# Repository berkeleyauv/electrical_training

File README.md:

# Underwater Robotics @ Berkeley | Electrical Training

Hello there! Welcome to UR@B electrical team! UR@B Electrical training will introduce you to basic circuit concepts, and firmware. Additionally, the HOPE Decal content created by IEEE @ Berkeley will introduce you to printed circuit board CAD tools. 

> "*Note: Feel free too ask/wait for a electrical team member to help you when working on this training to prevent frustration.*"

> "*Note: If you already feel comfortable with all the concepts below, feel free to skip this whole training all together and work on the project*"

### Prerequisites:
- None

At the end of the training, you will know: 

1. Basic Circuit (Electronic) Concepts
2. Basic Printed Circuit Board Design (PCB) CAD Tools 

### High Level View:

In the electrical team, you will be creating the electronics and the associated software to make it work. 

<br>

> "*Note: For each part, click on the dropdown to show the content.*"

# Prelab: Electronics (Hardware) - Part 1

You will learn about the concept of ground, voltage, current and various machine tools used in electrical engineering. 

<details>
<summary>Electronics Dropdown</summary>

## Current
Current is the rate at which electrons (particles) flow. Remember that particles are physical in nature. 

## Voltage 
Particles will stay still unless there is enough pressure to get them moving. Voltage is the difference in electric potential energy between two points. 
It is the **"Push"** that gives pressure to push electrons (particles) through a circuit. 

## Reference Voltage (Ground) 

Reference voltage commonly referred to as **ground** is a value that can be used with respect to everything else. 
One example is that "Earth ground" can be used as the reference voltage but most times the reference voltage is relative to the application. 

</br>

**"Common" ground** is the reference voltage that is shared across
the whole application. 

> **V_GND = 0 V**

Most times, zero volts are used as the reference voltage to make calculations easier.  

Note that the reference voltage may not necessarily be 0 volts, It can be any value as long as the circuit designer is consistent. 

## Resistance
Resistance is the opposition to the flow of current. Everything has resistance including wires itself. 

## Ohm Law

Image Credits: Build-electronics-circuit / Oyvind Nydal Dahl

</br>

Bringing it all together with Ohm's Law.  

> Voltage = Current * Resistance
 
> Current = Voltage / Resistance

> Resistance = Voltage / Current 

## Hardware Equipment
> Note: Please ask if you are interested in getting hands on experience with these machines.

### Power Supply Unit
Power supply unit provide a voltage source. 

### Multimeter
Measures Voltage, Current, and Resistance.

### Oscilloscope
Mainly used for tracking "signals". Signals are just voltage values. Oscilloscope is a multimeter but is able to provide a graph of the signal over time. 

</details>

> Checkpoint: No Checkpoint for Part 1

# Datasheet - Part 2 
When you are making anything, you are often not creating everything from scratch. You will need to use technical manuals, reference sheets, datasheets to know various features of "devices" that you plan on using in a design.

For example, consider a LED. 

There is a voltage value that the LED must be used to get the LED to turn on. This voltage value is called the "forward voltage". 
Consider: https://learn.adafruit.com/all-about-leds/the-led-datasheet
If you look at the datasheet, you will find that the "forward voltage" is 1.85V. That means the voltage difference across the LED should be that voltage value.

Note: Classes, Search engines, and books are your best friend in figuring out what various attributes you need to know when designing. 

Naturally, you are effectively required to search for information on your own because no one knows the exact information that is required.

Additionally, to make the LED work, you need to add a resistor. The point of the resistor is to limit the current. `R = 150Ohm - 300 Ohm` will work. The resistance depends on how intense the LED you want and minimum LED values.

# PCB ECAD Tools - KICAD - Part 3

Instead of using prototyping boards like stripboards and breadboards, you will now create a "PCB" which makes your electronics much more versatile. Instead of wires failing off, the wires can't fall off printed circuit boards. Like how 3D Printing design uses CAD tools like Solidworks, electrical engineers use electronic computer aided design (ECAD) like KiCad. 

<details>
<summary>PCB ECAD Tools Dropdown</summary>

To get used to the KiCad ECAD software, please follow the HOPE course. 
#### Hands on PCB Engineering (HOPE) | IEEE @ Berkeley
IEEE @ Berkeley has created an awesome decal (course) on printed circuit board design. All content and credit goes to HOPE staff!

See HOPE Decal- https://ieee.berkeley.edu/hope/
If the link does not work, please search for: IEEE Berkeley HOPE Decal
<br>

<h1>Disclaimer: We use "Altium Designer" </h1>
<b>But doing the training in KiCad is much easier. Altium is just another
ECAD tool but it isn't that intuitive to use. </b>

</br>

**For underwater robotics, Please do the following content and associated labs:**
1. Install Kicad
2. Light Sensor Schematic
3. Light Sensor Components
4. Light Sensor Layout
5. USB Charger Components (Optional)
6. USB Charger Schematic (Optional)
7. USB Charger Layout (Optional)

</details>

> Checkpoint: The DRC for both schematic/layout should show no errors. DRC - Design Rule Checker.

# Design
We did not at all cover the "Design" aspect of electrical engineering, searching for answers through your coursework, using search engines, and asking questions are the best way to learn "Design". 

Here are some keywords that outlines the steps to make a design work:
1. Planning
2. Tapeout
3. Bringup
4. Implementation

# Notes
The training and project is not meant to be comprehensive. Hopefully the training and project is good enough as a launchpad for you to further investigate engineering.

# Other:

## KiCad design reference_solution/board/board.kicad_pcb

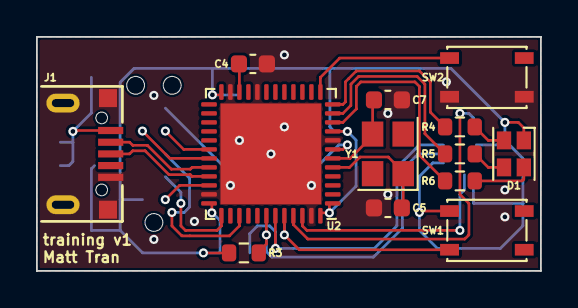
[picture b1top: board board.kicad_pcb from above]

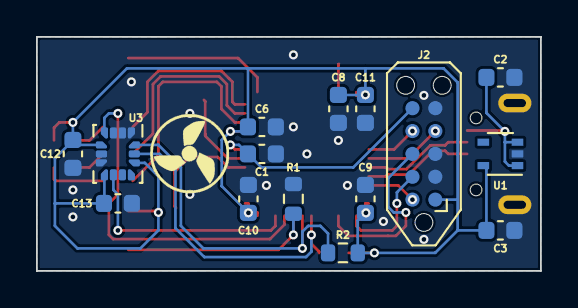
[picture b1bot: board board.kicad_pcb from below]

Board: 2 copper layers, 28.0 x 13.0 mm, 29 parts (16 on the bottom side), 26 nets.

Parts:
C1, C6, C8, C9, C10, C12, C13: 100n; C_0603_1608Metric
C2, C3: 1u; C_0603_1608Metric
C4, C11: 4.7u; C_0603_1608Metric
C5, C7: 20p; C_0603_1608Metric
D1: LED_ARGB; LED_Cree-PLCC4_2x2mm_CW
H1: logo; auv_logo
J1: USB_B_Micro; USB_Micro-B_U254-05
J2: SWD/UART; Tag-Connect_TC2050-IDC-NL_2x05_P1.27mm_Vertical
R1, R2, R3: 10k; R_0603_1608Metric
R4, R5, R6: 150; R_0603_1608Metric
SW1: BOOT0; SW_SPST_PTS810
SW2: USR; SW_SPST_PTS810
U1: MIC5365-3.3YC5; SOT-353_SC-70-5
U2: STM32F401CEUx; QFN-48-1EP_7x7mm_P0.5mm_EP5.6x5.6mm
U3: LSM6DSM; LGA-14_3x2.5mm_P0.5mm_LayoutBorder3x4y
Y1: 8MHz; Crystal_SMD_3225-4Pin_3.2x2.5mm

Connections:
+3V3: C3.1, C6.2, C8.1, C9.1, C10.1, C11.1, C12.1, C13.1, D1.1 (A), J2.1, R2.2, R3.2, SW1.2 (B), U1.5 (VOUT), U2.1 (VBAT), U2.9 (VREF+), U2.24 (VDD), U2.36 (VDD), U2.48 (VDD), U3.5 (VDDIO), U3.8 (VDD), U3.12 (CS)
+5V: C2.2, J1.1 (VBUS), U1.1 (VIN), U1.3 (EN)
/BOOT0: R1.1, SW1.1 (A), U2.44 (BOOT0)
/D+: J1.3 (D+), U2.33 (PA12)
/D-: J1.2 (D-), U2.32 (PA11)
/INT1: U2.45 (PB8), U3.4 (INT1)
/INT2: U2.46 (PB9), U3.9 (INT2)
/LED_B: R4.1, U2.12 (PA2)
/LED_G: R5.1, U2.11 (PA1)
/LED_R: R6.1, U2.10 (PA0)
/NRST: C1.1, J2.6, U2.7 (NRST)
/RX: J2.4, U2.31 (PA10)
/SCL: R3.1, U2.42 (PB6), U3.13 (SCL)
/SDA: R2.1, U2.43 (PB7), U3.14 (SDA)
/SWCLK: J2.9, U2.37 (PA14)
/SWDIO: J2.10, U2.34 (PA13)
/SWO: J2.8, U2.39 (PB3)
/TX: J2.7, U2.30 (PA9)
/USR_BUT: SW2.2 (B), U2.13 (PA3)
GND: C1.2, C2.1, C3.2, C4.1, C5.1, C6.1, C7.2, C8.2, C9.2, C10.2, C11.2, C12.2, C13.2, J1.5 (GND), J1.6 (Shield), J2.2, J2.3, J2.5, R1.2, SW2.1 (A), U1.2 (GND), U2.8 (VSSA), U2.20 (PB2), U2.23 (VSS), U2.35 (VSS), U2.47 (VSS), U2.49 (VSS), U3.1 (SDO/SA0), U3.2 (SDX), U3.3 (SCX), U3.6 (GND), U3.7 (GND)
unnamed: C4.2, U2.22 (VCAP1)
unnamed: C5.2, U2.5 (PH0), Y1.1
unnamed: C7.1, U2.6 (PH1), Y1.3
unnamed: D1.2 (RK), R6.2
unnamed: D1.3 (GK), R5.2
unnamed: D1.4 (BK), R4.2

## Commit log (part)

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2022-01-04 WIP reference solution
2022-01-05 ref soln wip
2022-01-05 finished schematic
2022-01-05 finished layout
2022-01-05 finish hardware side of ref soln
2022-01-22 added firmware writeup
2024-08-28 Starting the revamp of electrical training
2024-08-28 setting up the overall training
2024-08-28 finished part 1
2024-08-28 working on the firmware part
2024-08-28 fixing some syntax issues
2024-08-28 completed the diagram for firmware
2024-08-28 added some content at the other info
2024-09-24 fixing the RP2040 proj instruction in the training so that it uses clone instead of fork
2024-09-24 fixing some typos
